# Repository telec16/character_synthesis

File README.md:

# Character Synthesis using Fourier Transform

Based on http://www.glensstuff.com/fouriersynthchargen/fouriersynthchargen.htm

## Front Panel

The front panel was made with Galva ( http://www.f5bu.fr/galva-download/ ), in French.

## Clock generation board

~/!\ DIVoddN is not synthetizable with Lattice LSE. I use Synplify Pro.~ Actually I don't know what's going on, but it does not correspond to the simulation. The hardware tests show no errors.

### FPGA pinmap

| Name 		| Pin Number | Pin Name | Location  |
|-----------|------------|----------|-----------|
| clk_1M2	| 13		 | PCLKT2_1	| X1.3		|
| clrn		| 14		 | PCLKC2_1	| J4.1		|
| clk_20k	| 8			 | CSSPIN	| J2.5		|
| clk_40k	| 9			 | MCLK		| J2.4		|
| clk_60k	| 10		 | SPISO	| J2.3		|
| clk_80k	| 11		 | PCLKT2_0	| J2.2		|
| clk_100k	| 12		 | PCLKC2_0	| J2.1		|
| E1A		| 16		 | SN		| SW1.1		|
| E1B		| 17		 | SPISI	| SW1.3		|
| E2A		| 20		 | PCLKC1_0	| SW2.1		|
| E2B		| 21		 | PCLKT1_0	| SW2.3		|
| blanking  | 5			 | PCLKC3_0	| J2.6		|
| led 		| 23		 | DONE		| D2		|
| pin1		| 28		 | SCL		| J2.8		|
| pin2		| 4			 | PCLKT3_0	| J2.7		|
| TDO		| 1			 | TDO		| J1.5		|
| TDI		| 32		 | TDI		| J1.3		|
| TCK		| 30		 | TCK		| J1.2		|
| TMS		| 29		 | TMS		| J1.1		|

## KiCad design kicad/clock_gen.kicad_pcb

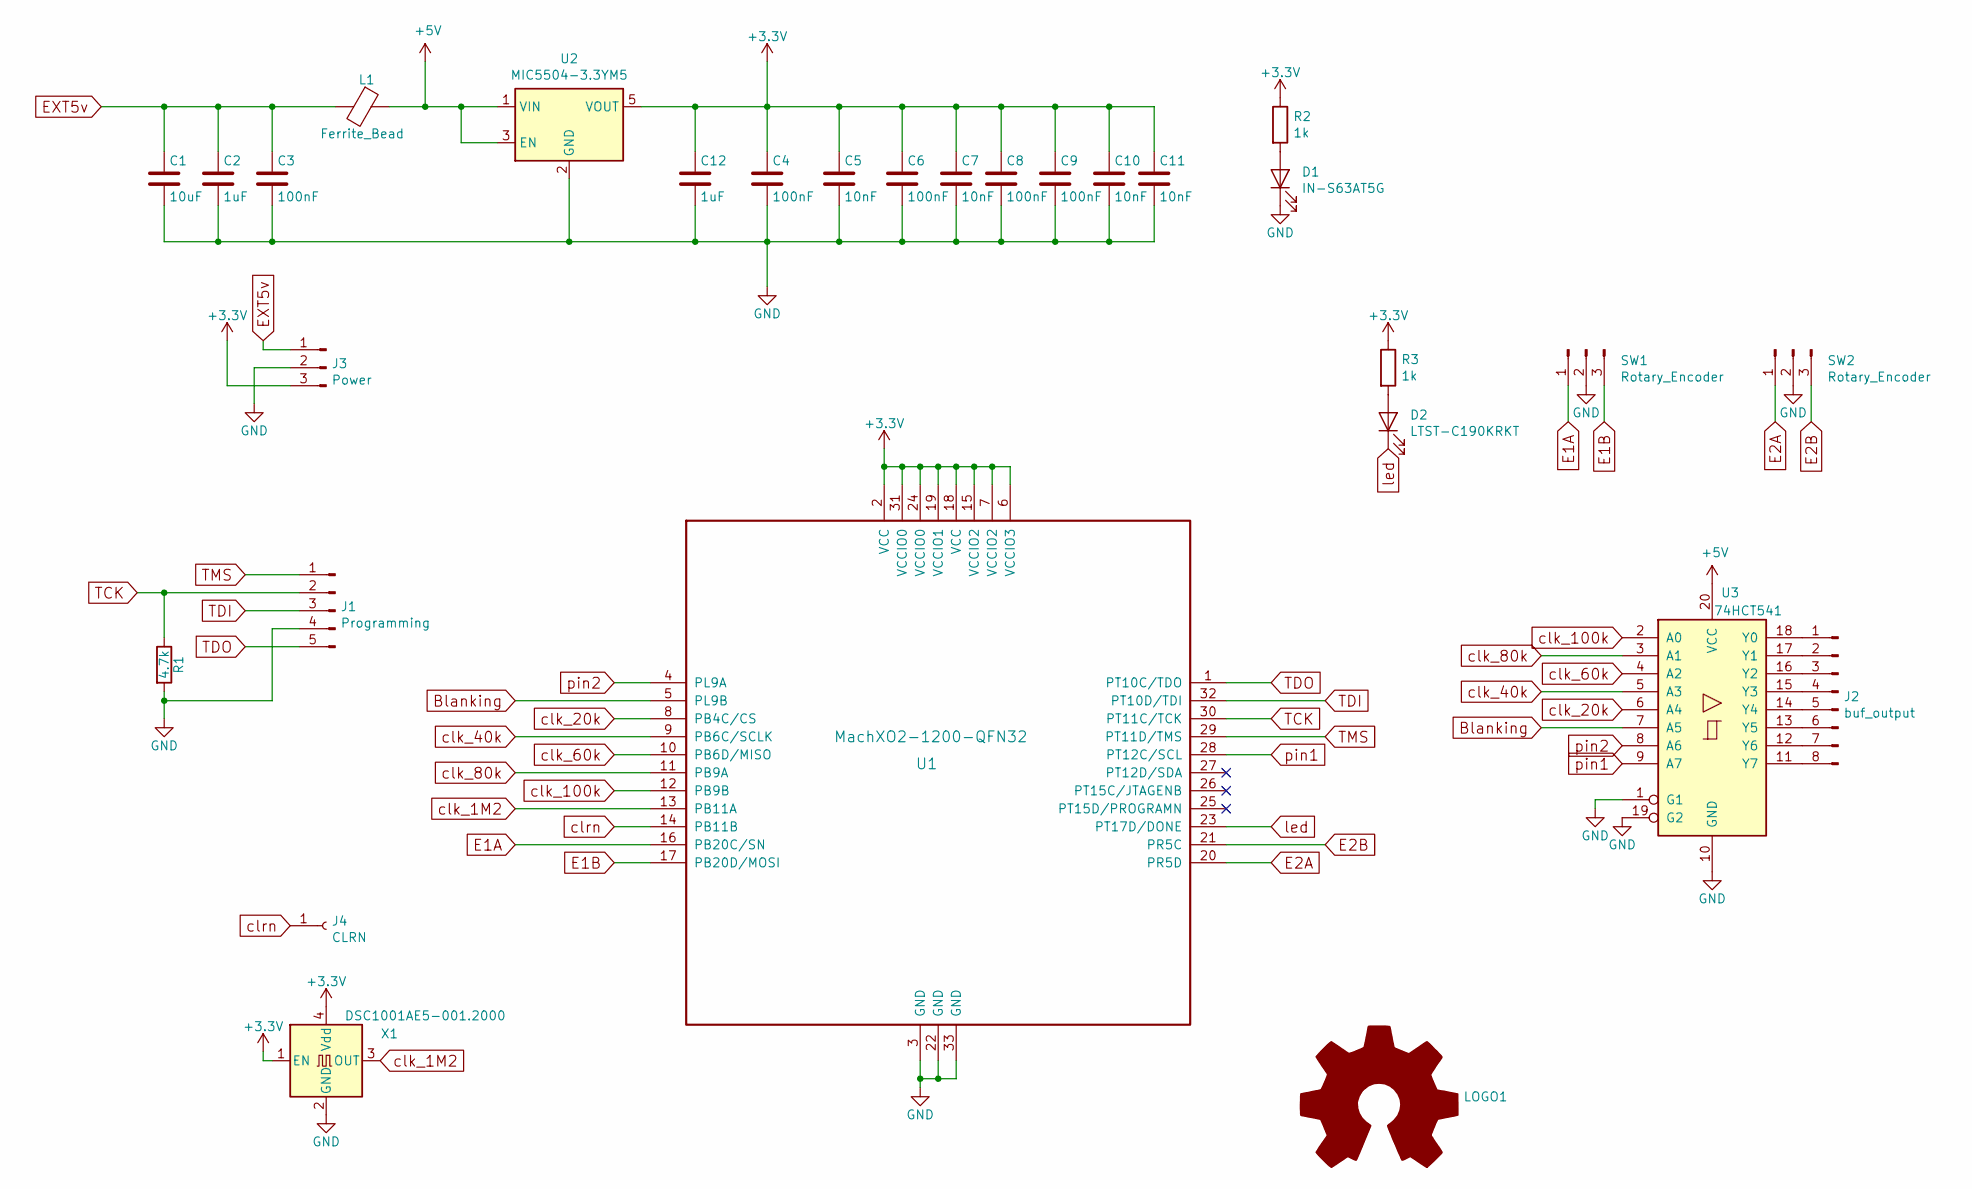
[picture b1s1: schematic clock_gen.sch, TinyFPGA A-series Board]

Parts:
C1: 10uF; C_0603_1608Metric
C2, C12: 1uF; C_0603_1608Metric
C3, C4, C6, C8, C9: 100nF; C_0603_1608Metric
C5, C7, C10, C11: 10nF; C_0603_1608Metric
D1: IN-S63AT5G; LED_0603_1608Metric
D2: LTST-C190KRKT; LED_0603_1608Metric
J1: Programming; PinHeader_1x05_P2.54mm_Vertical
J2: buf_output; PinHeader_1x08_P1.27mm_Vertical
J3: Power; PinHeader_1x03_P1.27mm_Vertical
J4: CLRN; PinHeader_1x01_P1.27mm_Vertical
L1: Ferrite_Bead; L_0603_1608Metric
LOGO1: Logo_Open_Hardware_Large; clk
R1: 4.7k; R_0603_1608Metric
R2, R3: 1k; R_0603_1608Metric
SW1, SW2: Rotary_Encoder; PinHeader_1x03_P1.27mm_Vertical
U1: MachXO2-1200-QFN32; QFN-32-1EP_5x5mm_P0.5mm_EP3.1x3.1mm_ThermalVias
U2: MIC5504-3.3YM5; SOT-23-5
U3: 74HCT541; SOIC-20W_7.5x12.8mm_P1.27mm
X1: DSC1001AE5-001.2000; Oscillator_SMD_EuroQuartz_XO91-4Pin_7.0x5.0mm

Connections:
+3V3: C4.1, C5.1, C6.1, C7.1, C8.1, C9.1, C10.1, C11.1, C12.1, J3.3, R2.1, R3.1, U1.2 (VCC), U1.6 (VCCIO3), U1.7 (VCCIO2), U1.15 (VCCIO2), U1.18 (VCC), U1.19 (VCCIO1), U1.24 (VCCIO0), U1.31 (VCCIO0), U2.5 (VOUT), X1.1 (EN), X1.4 (Vdd)
+5V: L1.1, U2.1 (VIN), U2.3 (EN), U3.20 (VCC)
Blanking: U1.5 (PL9B), U3.7 (A5)
E1A: SW1.1, U1.16 (PB20C/SN)
E1B: SW1.3, U1.17 (PB20D/MOSI)
E2A: SW2.1, U1.20 (PR5D)
E2B: SW2.3, U1.21 (PR5C)
EXT5v: C1.1, C2.1, C3.1, J3.1, L1.2
GND: C1.2, C2.2, C3.2, C4.2, C5.2, C6.2, C7.2, C8.2, C9.2, C10.2, C11.2, C12.2, D1.1 (K), J1.4, J3.2, R1.2, SW1.2, SW2.2, U1.3 (GND), U1.22 (GND), U1.33 (GND), U2.2 (GND), U3.1 (G1), U3.10 (GND), U3.19 (G2), X1.2 (GND)
unnamed: D1.2 (A), R2.2
unnamed: D2.2 (A), R3.2
unnamed: J2.1, U3.18 (Y0)
unnamed: J2.2, U3.17 (Y1)
unnamed: J2.3, U3.16 (Y2)
unnamed: J2.4, U3.15 (Y3)
unnamed: J2.5, U3.14 (Y4)
unnamed: J2.6, U3.13 (Y5)
unnamed: J2.7, U3.12 (Y6)
unnamed: J2.8, U3.11 (Y7)
TCK: J1.2, R1.1, U1.30 (PT11C/TCK)
TDI: J1.3, U1.32 (PT10D/TDI)
TDO: J1.5, U1.1 (PT10C/TDO)
TMS: J1.1, U1.29 (PT11D/TMS)
clk_1M2: U1.13 (PB11A), X1.3 (OUT)
clk_20k: U1.8 (PB4C/CS), U3.6 (A4)
clk_40k: U1.9 (PB6C/SCLK), U3.5 (A3)
clk_60k: U1.10 (PB6D/MISO), U3.4 (A2)
clk_80k: U1.11 (PB9A), U3.3 (A1)
clk_100k: U1.12 (PB9B), U3.2 (A0)
clrn: J4.1, U1.14 (PB11B)
led: D2.1 (K), U1.23 (PT17D/DONE)
pin1: U1.28 (PT12C/SCL), U3.9 (A7)
pin2: U1.4 (PL9A), U3.8 (A6)

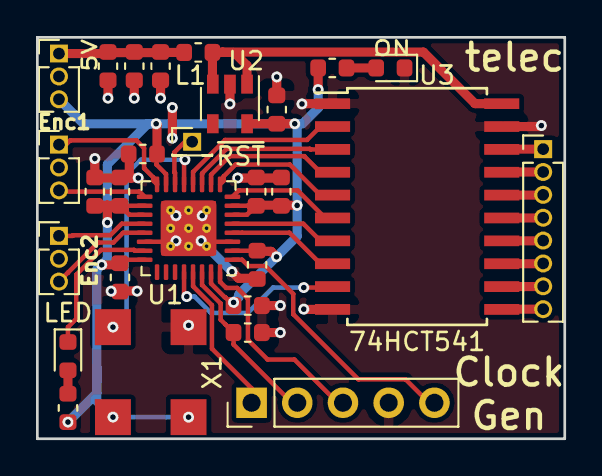
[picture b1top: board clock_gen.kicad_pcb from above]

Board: 2 copper layers, 29.3 x 22.3 mm, 29 parts (1 on the bottom side), 33 nets.

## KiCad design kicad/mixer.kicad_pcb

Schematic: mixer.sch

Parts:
C1, C2: 1u; C_1206_3216Metric_Pad1.42x1.75mm_HandSolder
D1, D2: LED; LED_D4.0mm
J1: Power; PinHeader_1x03_P2.54mm_Vertical
J2: X input; PinHeader_1x10_P2.54mm_Vertical
J3: X offset; PinHeader_1x01_P2.54mm_Vertical
J4: Y input; PinHeader_1x10_P2.54mm_Vertical
J5: Y offset; PinHeader_1x01_P2.54mm_Vertical
J6: Output; PinHeader_1x02_P2.54mm_Vertical
R1, R2: 3k3; R_Axial_DIN0204_L3.6mm_D1.6mm_P7.62mm_Horizontal
R3, R4, R5, R6, R7, R8, R9, R10, R11, R12, R13, R16, R17, R18, R19, R20, R21, R22, R23, R24, R25, R26: 100k; R_Axial_DIN0204_L3.6mm_D1.6mm_P7.62mm_Horizontal
R14, R27: 1k; R_Axial_DIN0204_L3.6mm_D1.6mm_P2.54mm_Vertical
R15, R28: 1k; R_Axial_DIN0204_L3.6mm_D1.6mm_P7.62mm_Horizontal
RV1, RV2: 10k; Potentiometer_Bourns_3386F_Vertical
U1: TL084; DIP-14_W7.62mm_LongPads

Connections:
+15V: C1.1, D1.2 (A), J1.1, U1.4
-15V: C2.2, D2.1 (K), J1.3, U1.11
/X: J6.1, RV1.3, U1.7
/Xi: R3.1, R4.1, R5.1, R6.1, R7.1, R8.1, R9.1, R10.1, R11.1, R12.1, R13.2, U1.2
/Xo: J3.1, U1.5
/Y: J6.2, RV2.1, U1.8
/Yi: R16.1, R17.1, R18.1, R19.1, R20.1, R21.1, R22.1, R23.1, R24.1, R25.1, R26.2, U1.13
/Yo: J5.1, U1.10
GND: C1.2, C2.1, J1.2, R1.1, R2.1, U1.3, U1.12
unnamed: D1.1 (K), R1.2
unnamed: D2.2 (A), R2.2
unnamed: J2.1, R3.2
unnamed: J2.2, R5.2
unnamed: J2.3, R7.2
unnamed: J2.4, R9.2
unnamed: J2.5, R11.2
unnamed: J2.6, R4.2
unnamed: J2.7, R6.2
unnamed: J2.8, R8.2
unnamed: J2.9, R10.2
unnamed: J2.10, R12.2
unnamed: J4.1, R16.2
unnamed: J4.2, R18.2
unnamed: J4.3, R20.2
unnamed: J4.4, R22.2
unnamed: J4.5, R24.2
unnamed: J4.6, R17.2
unnamed: J4.7, R19.2
unnamed: J4.8, R21.2
unnamed: J4.9, R23.2
unnamed: J4.10, R25.2
unnamed: R13.1, R15.2, U1.1
unnamed: R14.1, RV1.1, RV1.2
unnamed: R14.2, R15.1, U1.6
unnamed: R26.1, R28.2, U1.14
unnamed: R27.1, RV2.2, RV2.3
unnamed: R27.2, R28.1, U1.9

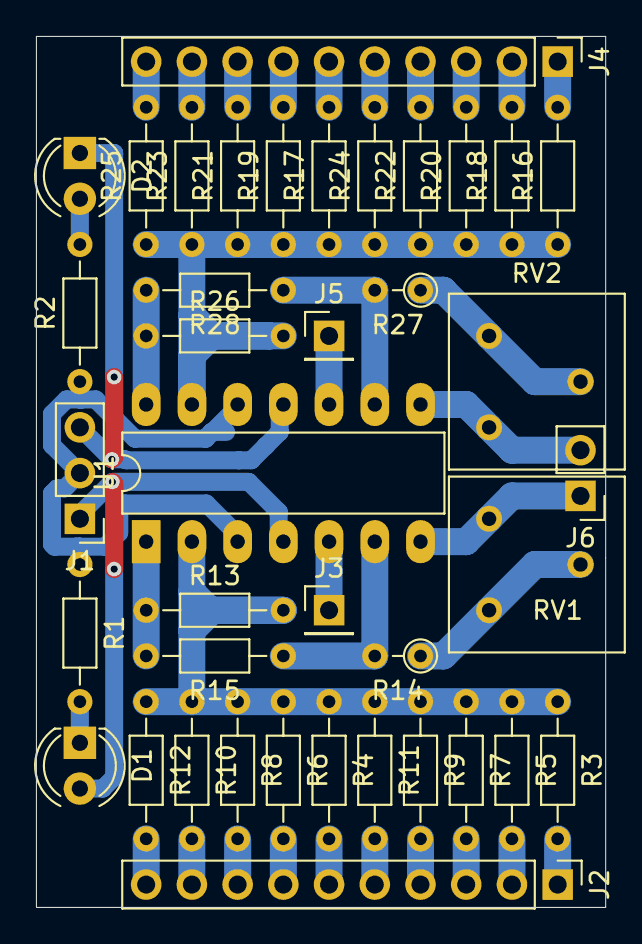
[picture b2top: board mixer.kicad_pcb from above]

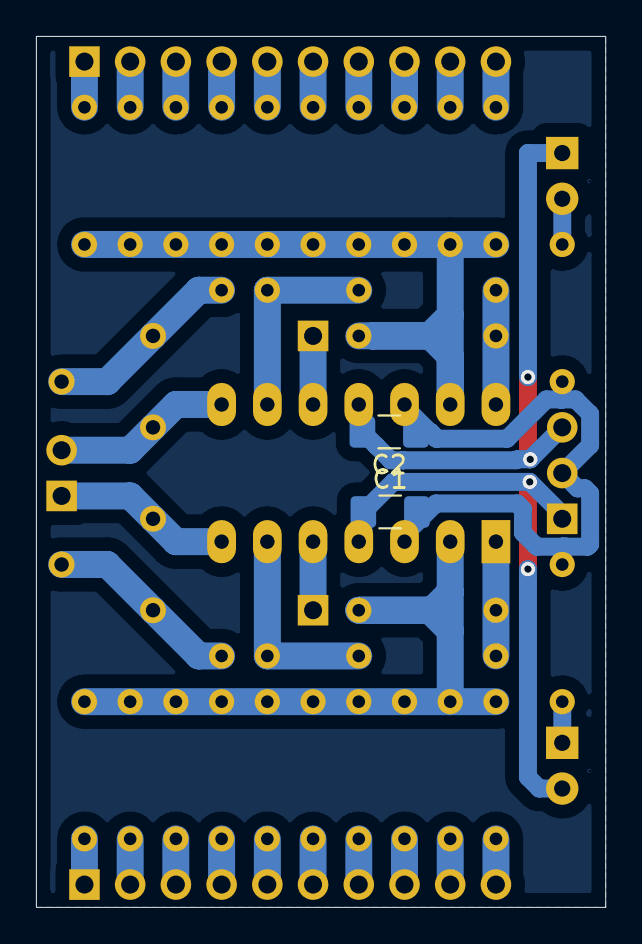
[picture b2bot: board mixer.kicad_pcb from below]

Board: 2 copper layers, 31.6 x 48.4 mm, 41 parts (2 on the bottom side), 37 nets.

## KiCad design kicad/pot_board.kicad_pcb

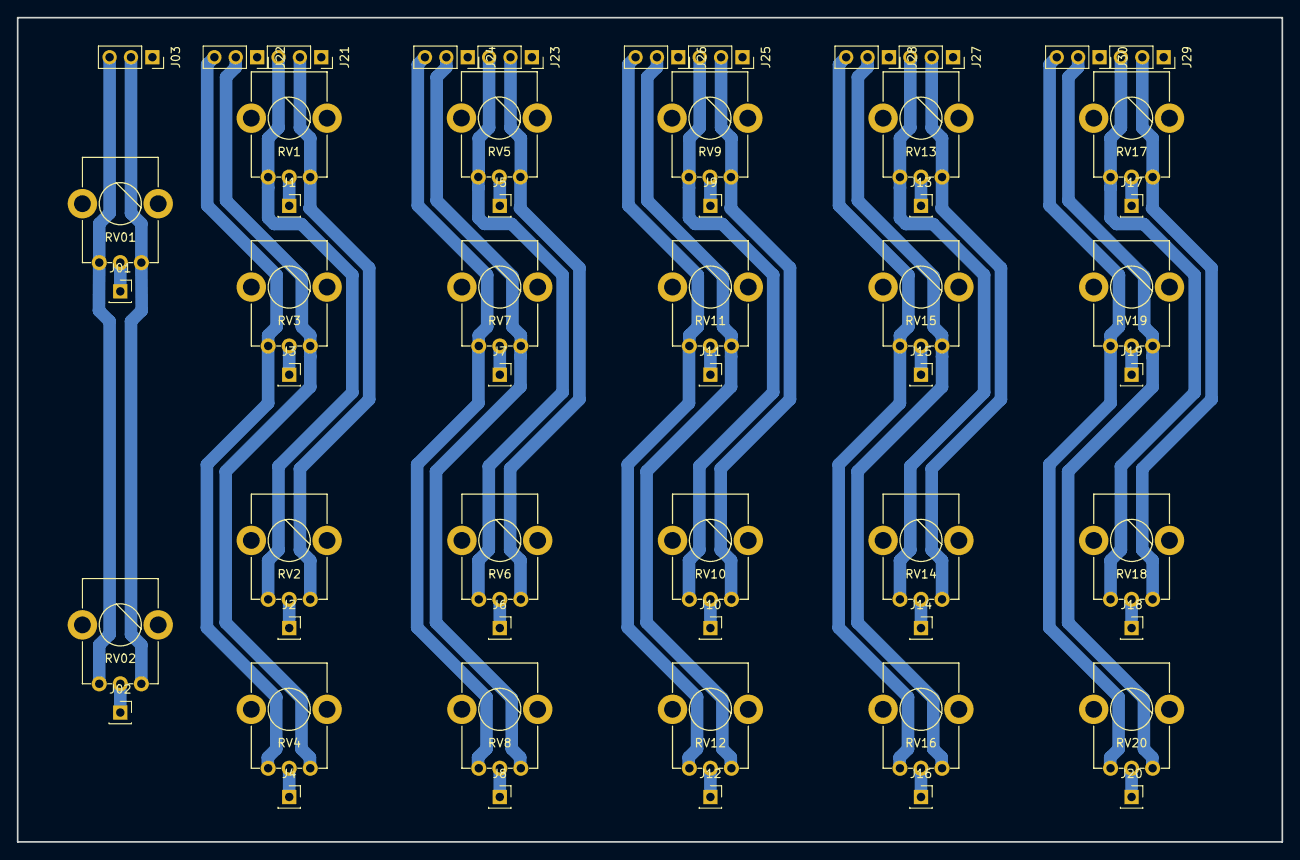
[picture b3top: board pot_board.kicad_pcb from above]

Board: 2 copper layers, 150.2 x 97.9 mm, 55 parts (0 on the bottom side), 45 nets.

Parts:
J01, J1, J02, J2, J3, J4, J5, J6, J7, J8, J9, J10, J11, J12, J13, J14, J15, J16, J17, J18, J19, J20: OUT; PinSocket_1x01_P2.54mm_Vertical
J03, J21, J22, J23, J24, J25, J26, J27, J28, J29, J30: IN; PinSocket_1x03_P2.54mm_Vertical
RV01, RV1, RV02, RV2, RV3, RV4, RV5, RV6, RV7, RV8, RV9, RV10, RV11, RV12, RV13, RV14, RV15, RV16, RV17, RV18, RV19, RV20: 10k; PTV09A

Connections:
GND: J03.1, J21.1, J22.1, J23.1, J24.1, J25.1, J26.1, J27.1, J28.1, J29.1, J30.1, RV01.4, RV1.4, RV02.4, RV2.4, RV3.4, RV4.4, RV5.4, RV6.4, RV7.4, RV8.4, RV9.4, RV10.4, RV11.4, RV12.4, RV13.4, RV14.4, RV15.4, RV16.4, RV17.4, RV18.4, RV19.4, RV20.4
unnamed: J01.1, RV01.2
unnamed: J1.1, RV1.2
unnamed: J02.1, RV02.2
unnamed: J2.1, RV2.2
unnamed: J3.1, RV3.2
unnamed: J03.2, RV01.3, RV02.3
unnamed: J03.3, RV01.1, RV02.1
unnamed: J4.1, RV4.2
unnamed: J5.1, RV5.2
unnamed: J6.1, RV6.2
unnamed: J7.1, RV7.2
unnamed: J8.1, RV8.2
unnamed: J9.1, RV9.2
unnamed: J10.1, RV10.2
unnamed: J11.1, RV11.2
unnamed: J12.1, RV12.2
unnamed: J13.1, RV13.2
unnamed: J14.1, RV14.2
unnamed: J15.1, RV15.2
unnamed: J16.1, RV16.2
unnamed: J17.1, RV17.2
unnamed: J18.1, RV18.2
unnamed: J19.1, RV19.2
unnamed: J20.1, RV20.2
unnamed: J21.2, RV1.3, RV2.3
unnamed: J21.3, RV1.1, RV2.1
unnamed: J22.2, RV3.3, RV4.3
unnamed: J22.3, RV3.1, RV4.1
unnamed: J23.2, RV5.3, RV6.3
unnamed: J23.3, RV5.1, RV6.1
unnamed: J24.2, RV7.3, RV8.3
unnamed: J24.3, RV7.1, RV8.1
unnamed: J25.2, RV9.3, RV10.3
unnamed: J25.3, RV9.1, RV10.1
unnamed: J26.2, RV11.3, RV12.3
unnamed: J26.3, RV11.1, RV12.1
unnamed: J27.2, RV13.3, RV14.3
unnamed: J27.3, RV13.1, RV14.1
unnamed: J28.2, RV15.3, RV16.3
unnamed: J28.3, RV15.1, RV16.1
unnamed: J29.2, RV17.3, RV18.3
unnamed: J29.3, RV17.1, RV18.1
unnamed: J30.2, RV19.3, RV20.3
unnamed: J30.3, RV19.1, RV20.1

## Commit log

2020-01-24 schematics
2020-01-26 Kicad files for the clocks source
2020-01-26 Lattice files for clocks gen
2020-02-08 Finished PCB
2020-02-08 ltspice files
2020-05-23 clock gen Minimal Working Example (tested)
2020-05-23 Changed to Synplify
2020-05-23 Added front panel files
2020-05-23 Encoder structure
2020-05-25 Changed div files to produce good signals. Tested.
2020-05-25 Finished design, tests to be done
